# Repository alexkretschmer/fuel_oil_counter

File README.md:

# Fuel oil counter

Fuel oil counter with Modbus (operating hours counters to calculate the fuel oil consumption).
Calculation of the consumption based on the set nozzle liter consumption.

Full documentation
[Documentation Fuel oil counter](https://alexkretschmer.github.io/fuel_oil_counter/)

## Arduino libarys
please add EEPROM and ModbusRtu Libary in the Arduino IDE

## Parameter
operating voltage: 5V
output signal: RS-485
communication protocol: Modbus RTU
communication address: 1 ~ 247 (Standard 1)

## OpenHab example

openhab examples scripts:[openhab examples](openhab_examples/readme.md)

## programming table SW1

The factor for the calculation of the heating oil is set with the dip switch SW1.

| 1   | 2   | 3   | 4   | 5   | oil kg per hour|
|:---:|:---:|:---:|:---:|:---:|:--------------:|
| off | off | off | off | off | 1.45           |
| off | off | off | off | on  | 1.5            |
| off | off | off | on  | off | 1.55           |
| off | off | off | on  | on  | 1.6            |
| off | off | on  | off | off | 1.65           |
| off | off | on  | off | on  | 1.7            |
| off | off | on  | on  | off | 1.75           |
| off | off | on  | on  | on  | 1.8            |
| off | on  | off | off | off | 1.85           |
| off | on  | off | off | on  | 1.9            |
| off | on  | off | on  | off | 1.95           |
| off | on  | off | on  | on  | 2              |
| off | on  | on  | off | off | 2.05           |
| off | on  | on  | off | on  | 2.1            |
| off | on  | on  | on  | off | 2.15           |
| off | on  | on  | on  | on  | 2.2            |
| on  | off | off | off | off | 2.25           |
| on  | off | off | off | on  | 2.3            |
| on  | off | off | on  | off | 2.35           |
| on  | off | off | on  | on  | 2.4            |
| on  | off | on  | off | off | 2.45           |
| on  | off | on  | off | on  | 2.5            |
| on  | off | on  | on  | off | 2.55           |
| on  | off | on  | on  | on  | 2.6            |
| on  | on  | off | off | off | 2.65           |
| on  | on  | off | off | on  | 2.7            |
| on  | on  | off | on  | off | 2.75           |
| on  | on  | off | on  | on  | 2.8            |
| on  | on  | on  | off | off | 2.85           |
| on  | on  | on  | off | on  | 2.9            |
| on  | on  | on  | on  | off | 2.95           |
| on  | on  | on  | on  | on  | 3              |

## Modbus Protocol
### Function codes
        
|command register| function                  |
|----------------|---------------------------|
| 0x03           | read keep register        |
| 0x04           | read input register       |
| 0x06           | write a single register   |
| 0x10           | write more keep registers |

### Registers

|regsiter type   | register address | gegister contents   | bytes | register - ID  |
|----------------|------------------|---------------------|-------|----------------|
| input register | 0x0001           | ml summary Hi Byte  |   2   |  1             | 
| input register | 0x0002           | ml summary Low Byte |   2   |  2             | 
| input register | 0x0003           | s summary Hi Byte   |   2   |  3             | 
| input register | 0x0004           | s summary Low Byte  |   2   |  4             | 
| input register | 0x0005           | ms time   Hi Byte   |   2   |  5             | 
| input register | 0x0006           | ms time   Low Byte  |   2   |  6             |
| input register | 0x0007           | l summary           |   2   |  7 (EEPROM)    |
| input register | 0x0008           | h active summary    |   2   |  8 (EEPROM)    |
| debug register | 0x0009           | DIP value           |   2   |  9             |
| debug register | 0x0010           | gram per hour       |   2   |  10            |
| debug register | 0x0011           | ml per hour         |   2   |  11            |
| debug register | 0x0012           | fw version          |   2   |  12            |
| keep register  | 0x0013           | device address      |   2   |  13 (EEPROM)   |
| keep register  | 0x0014           | baud rate           |   2   |  14 (EEPROM)   |
| keep register  | 0x0015           | reset summary       |   2   |  15            |

baudrate = 0 =>  9600 baud
           1 => 14400 baud
           2 => 19200 baud

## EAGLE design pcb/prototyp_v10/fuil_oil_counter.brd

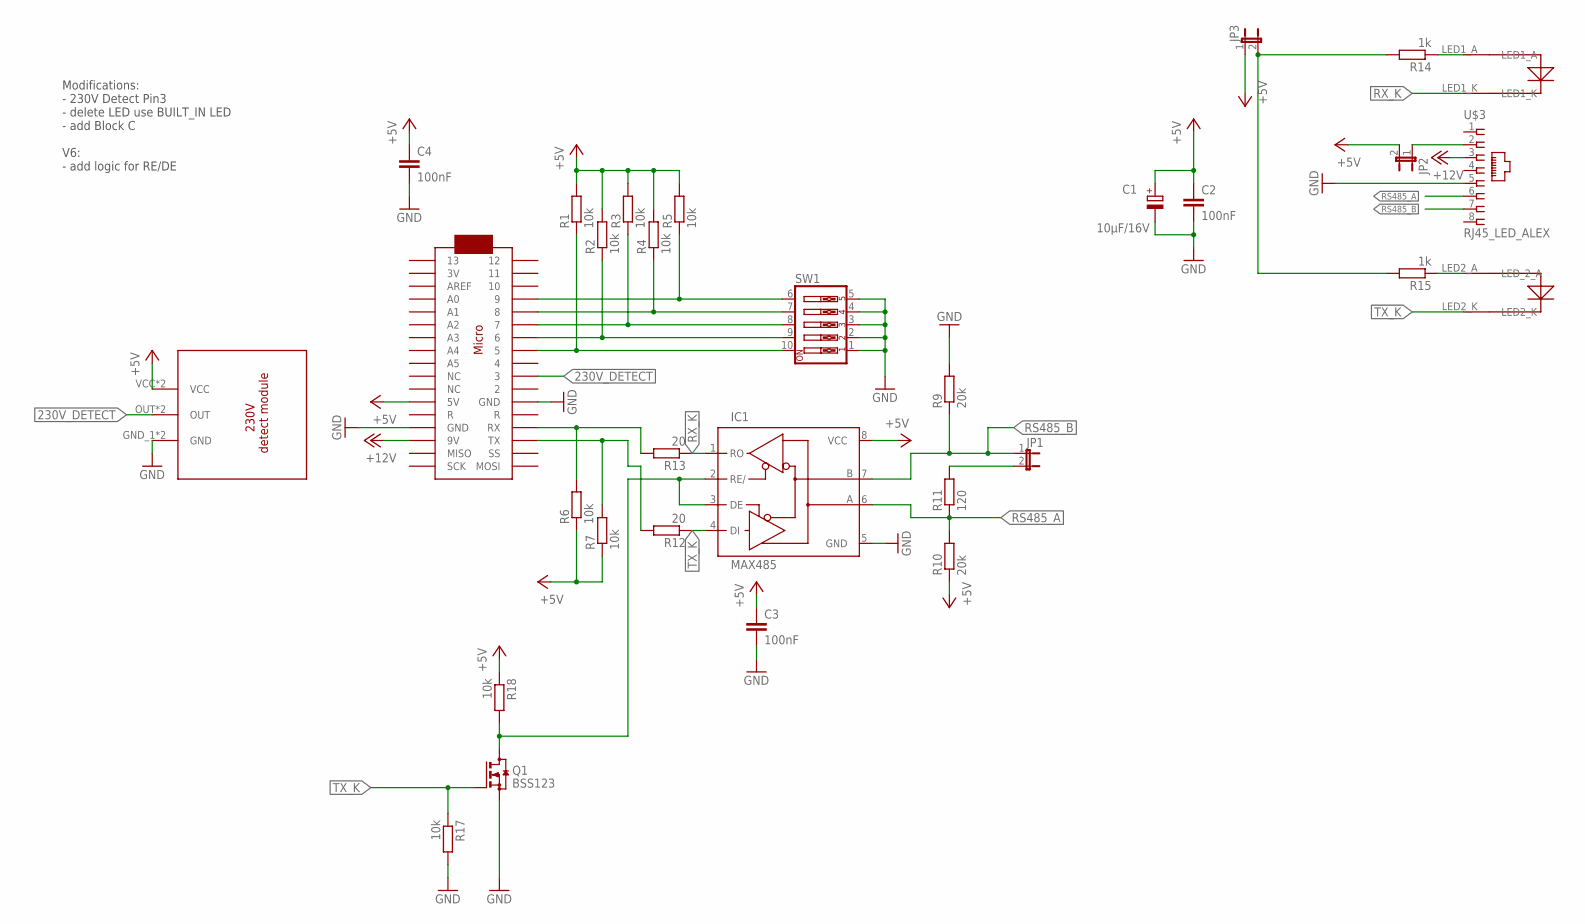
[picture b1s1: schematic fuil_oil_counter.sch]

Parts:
C1: 10µF/16V; SMC_C
C2, C3, C4: 100nF; C0805
IC1: MAX485; SO08
JP1, JP2, JP3: JP1E; JP1
Q1: BSS123; SOT23
R1, R2, R3, R4, R5, R6, R7, R17, R18: 10k; M0805
R9, R10: 20k; M0805
R11: 120; P0613/15
R12, R13: 20; M0805
R14, R15: 1k; M0805
SW1: SW_DIP-5; EDG-05
U$1: ARDUINOMICRO
U$2: POWER_DETECT
U$3: RJ45_LED_ALEX; RJ45-NO-SHIELD-WITH_LED

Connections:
230V_DETECT: U$1.P$10 (3), U$2.OUT, U$2.OUT_2 (OUT)
+5V: C1.+, C2.1, C3.1, C4.1, IC1.8 (VCC), JP2.2, JP3.1, R1.2, R2.2, R3.2, R4.2, R5.2, R6.1, R7.1, R10.1, R18.1, U$1.P$23 (5V), U$2.VCC, U$2.VCC_2 (VCC)
+12V: U$1.P$20 (9V), U$3.3
EN: IC1.2 (RE/), IC1.3 (DE), Q1.3 (D), R18.2
GND: C1.-, C2.2, C3.2, C4.2, IC1.5 (GND), Q1.2 (S), R9.2, R17.2, SW1.1, SW1.2, SW1.3, SW1.4, SW1.5, U$1.P$12 (GND), U$1.P$21 (GND), U$2.GND_1 (GND), U$2.GND_PIN (GND), U$3.5
unnamed: R1.1, SW1.10, U$1.P$8 (5)
unnamed: R2.1, SW1.9, U$1.P$7 (6)
unnamed: R3.1, SW1.8, U$1.P$6 (7)
unnamed: R4.1, SW1.7, U$1.P$5 (8)
unnamed: R5.1, SW1.6, U$1.P$4 (9)
unnamed: JP2.1, U$3.2
unnamed: JP1.2, R11.2
unnamed: R14.1, U$3.LED1_A
unnamed: R15.1, U$3.LED2_A (LED_2_A)
unnamed: R6.2, R13.2, U$1.P$14 (RX)
unnamed: R7.2, R12.2, U$1.P$15 (TX)
unnamed: JP3.2, R14.2, R15.2
RS485_A: IC1.6 (A), R10.2, R11.1, U$3.6
RS485_B: IC1.7 (B), JP1.1, R9.1, U$3.7
RX_K: IC1.1 (RO), R13.1, U$3.LED1_K
TX_K: IC1.4 (DI), Q1.1 (G), R12.1, R17.1, U$3.LED2_K

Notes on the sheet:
Modifications: - 230V Detect Pin3 - delete LED use BUILT_IN LED - add Block C V6: - add logic for RE/DE

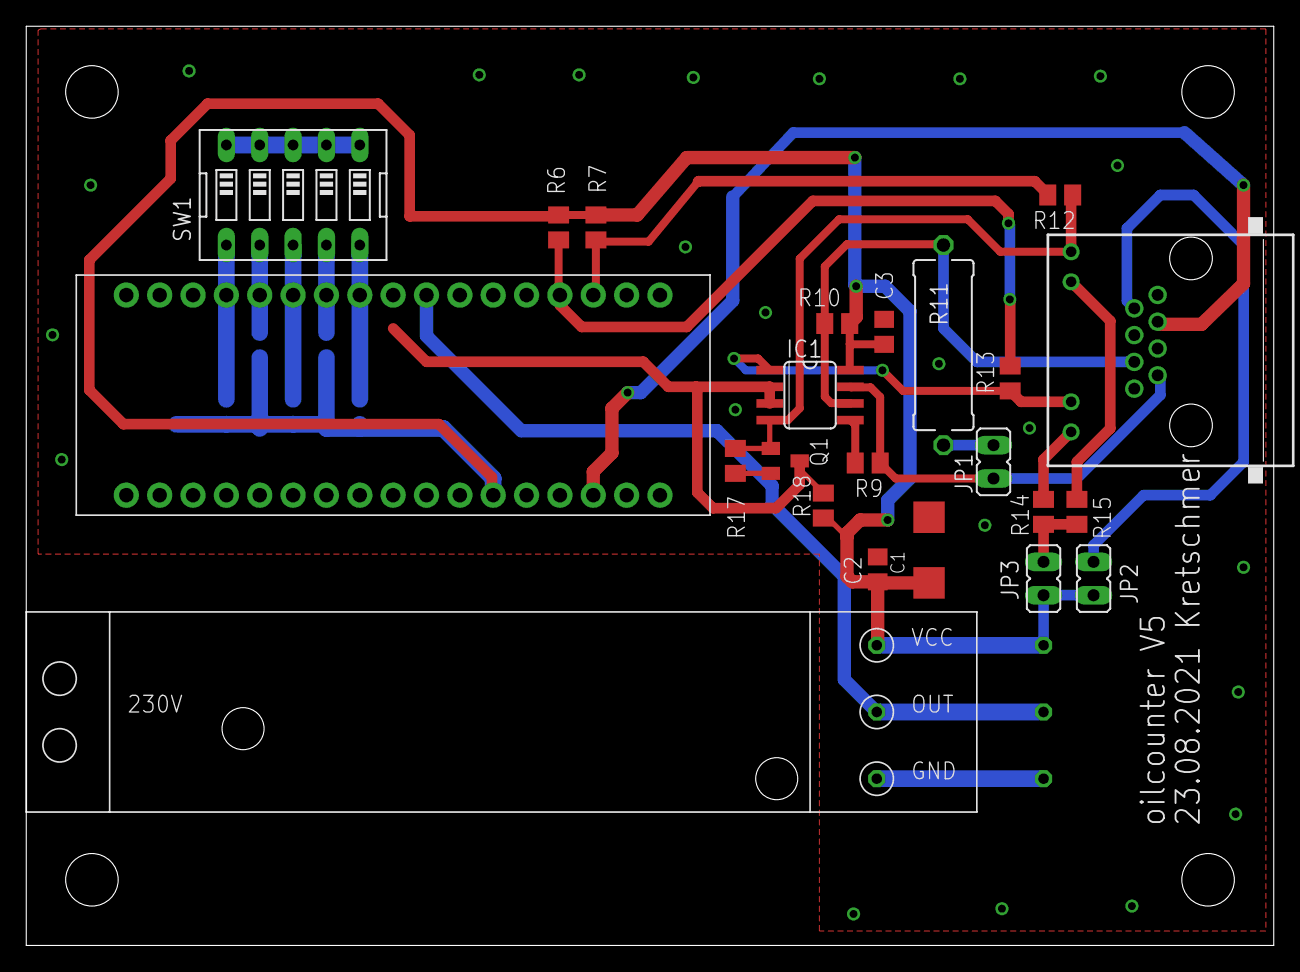
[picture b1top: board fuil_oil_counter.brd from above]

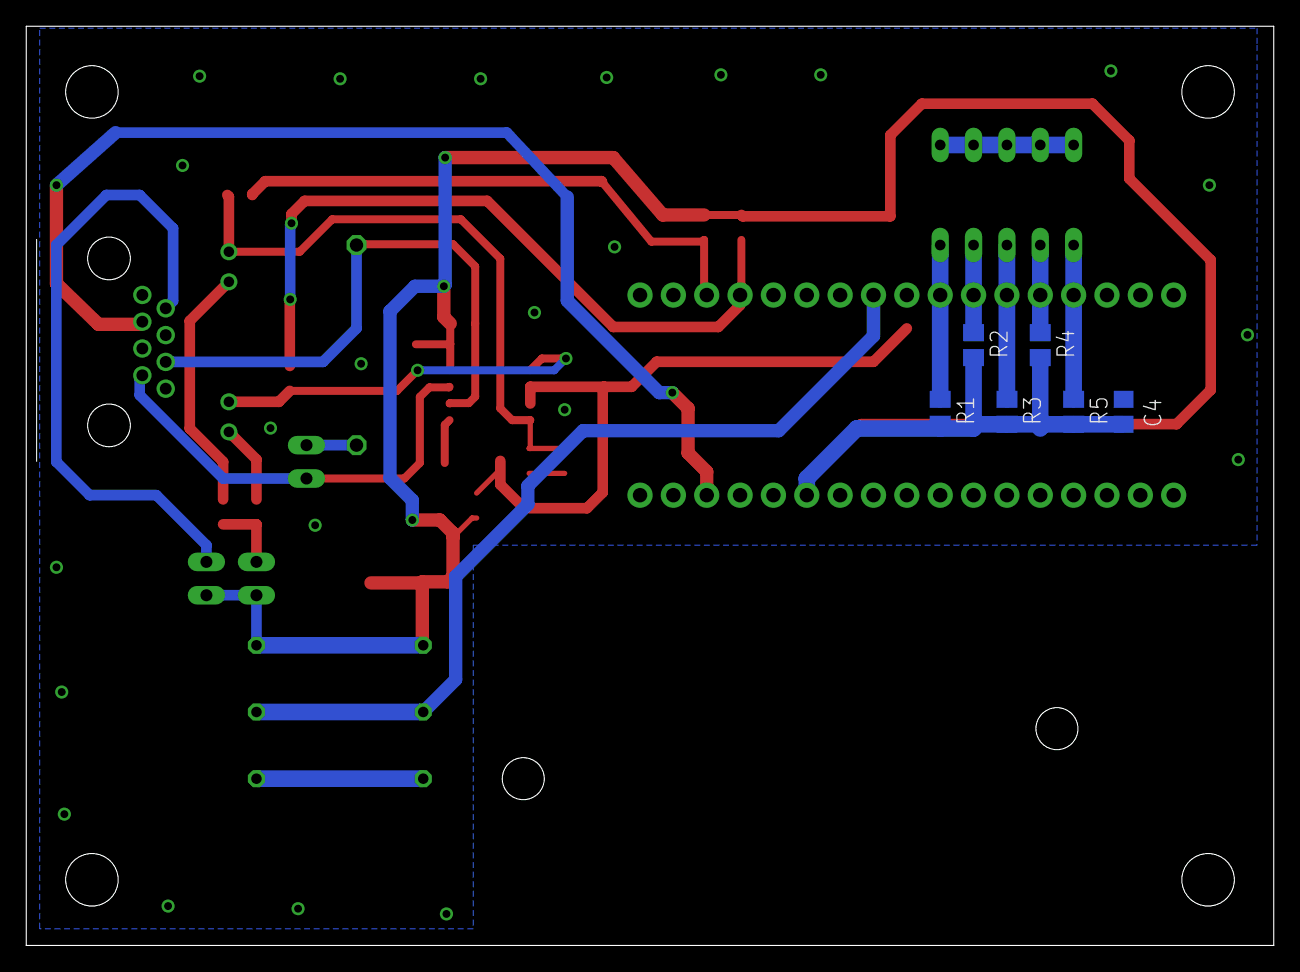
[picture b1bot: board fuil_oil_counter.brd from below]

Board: 2 copper layers, 95.0 x 70.0 mm, 29 parts (6 on the bottom side), 21 nets.

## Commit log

2022-05-27 modify readme and add pcb layout
2022-05-27 modify readme
2022-05-27 add programming table , moidfy pcb
2022-05-28 openhab examples
2022-05-28 fix fileextension
2022-05-28 fix link
2022-05-28 fix name
2022-05-31 add picture
2022-06-03 add git ignore
2022-06-03 add source code
2022-06-03 add libary infos
2026-01-04 docu
    add docu
2026-01-04 rename folder
2026-01-04 fix docu script path
2026-01-04 docu: add intro
2026-01-04 add hardware and firmware
2026-01-04 add some documentation
2026-01-04 add example docu
2026-01-04 add link
2026-01-04 add pic
2026-01-04 add buy me a coffee
2026-01-04 test buy me a coffee
2026-01-04 update docu
